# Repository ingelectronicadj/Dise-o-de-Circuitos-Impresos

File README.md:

# Repo Circuitos Impresos
Versionamiento de diversas placas PCB y diseños para integrados de soldadura superficial diseñados asiendo uso del software Eagle (Version Académica)

## IoT para determinar el peso al interior de un contenedor

## Estación Meteorologica remota - GSM

## Bases para sensor UV y de Color

## Control de 2 motores DC

## PCB para control de LED RGB 100W

## Modulador - Demodulador

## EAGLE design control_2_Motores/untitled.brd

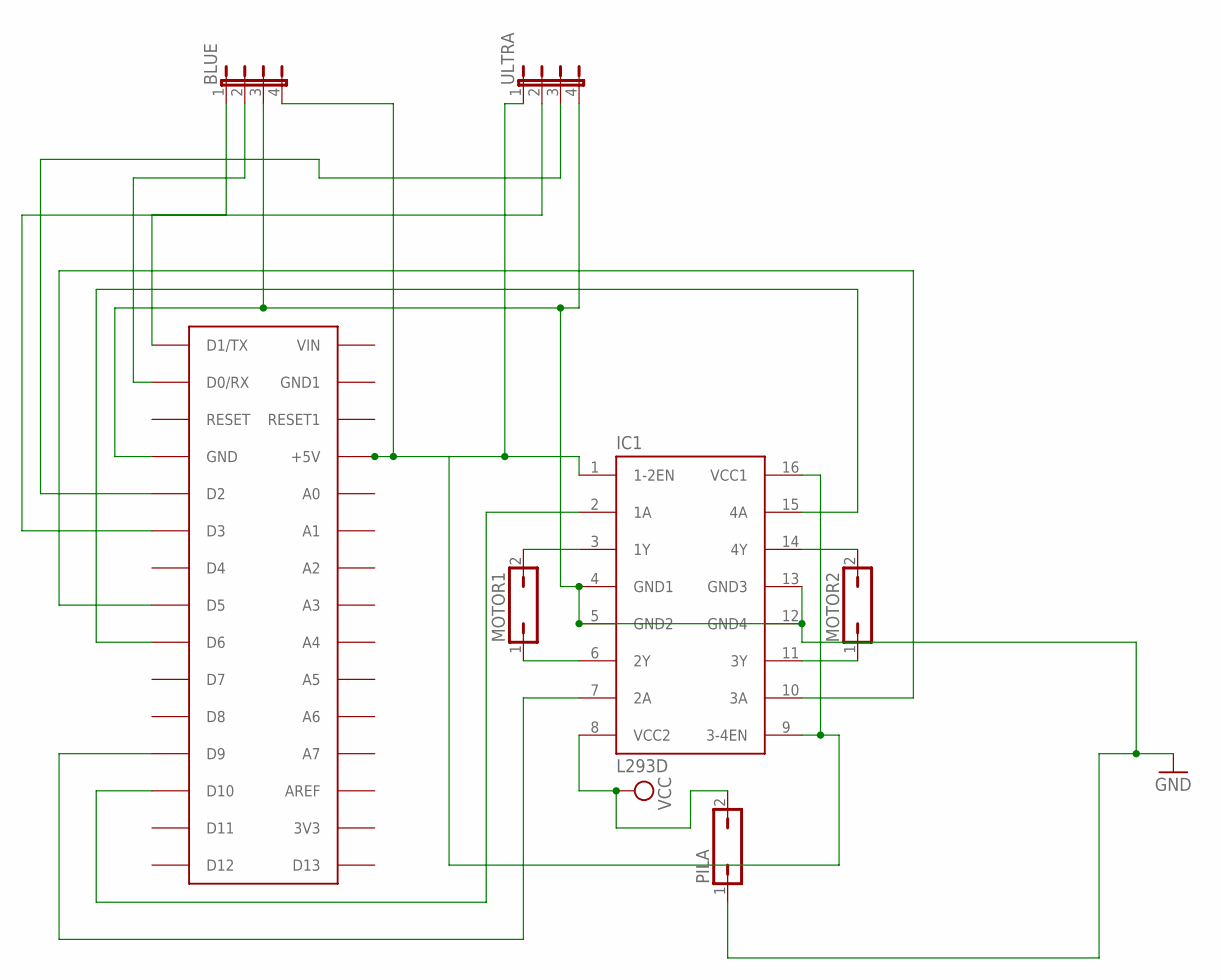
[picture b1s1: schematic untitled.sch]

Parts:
BLUE: JP4E; JP4
IC1: L293D; DIL16
MOTOR1, MOTOR2: JP1Q; JP1
PILA: JP1Q; JP1
U$1: ARDUINONANO; PDIP-32
ULTRA: JP4E; JP4

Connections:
GND: BLUE.3, IC1.4 (GND1), IC1.5 (GND2), IC1.12 (GND4), IC1.13 (GND3), PILA.1, U$1.GND, ULTRA.4
unnamed: IC1.10 (3A), U$1.D5
unnamed: IC1.15 (4A), U$1.D6
unnamed: IC1.7 (2A), U$1.D9
unnamed: IC1.2 (1A), U$1.D10
unnamed: BLUE.4, IC1.1 (1-2EN), IC1.9 (3-4EN), IC1.16 (VCC1), U$1.+5V, ULTRA.1
unnamed: BLUE.2, U$1.D0/RX
unnamed: BLUE.1, U$1.D1/TX
unnamed: IC1.3 (1Y), MOTOR1.2
unnamed: U$1.D3, ULTRA.2
unnamed: U$1.D2, ULTRA.3
unnamed: IC1.6 (2Y), MOTOR1.1
unnamed: IC1.11 (3Y), MOTOR2.1
unnamed: IC1.14 (4Y), MOTOR2.2
VCC: IC1.8 (VCC2), PILA.2

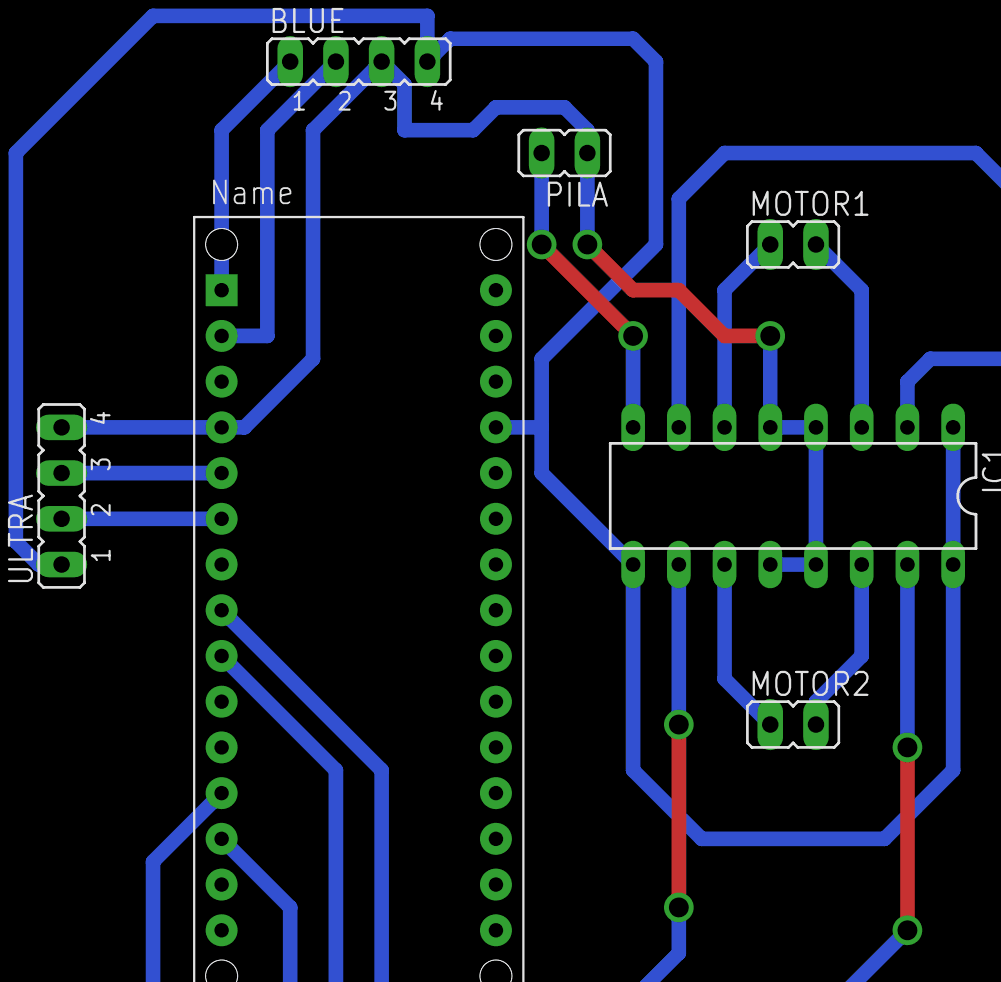
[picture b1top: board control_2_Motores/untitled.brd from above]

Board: 2 copper layers, 7 parts (0 on the bottom side), 15 nets.

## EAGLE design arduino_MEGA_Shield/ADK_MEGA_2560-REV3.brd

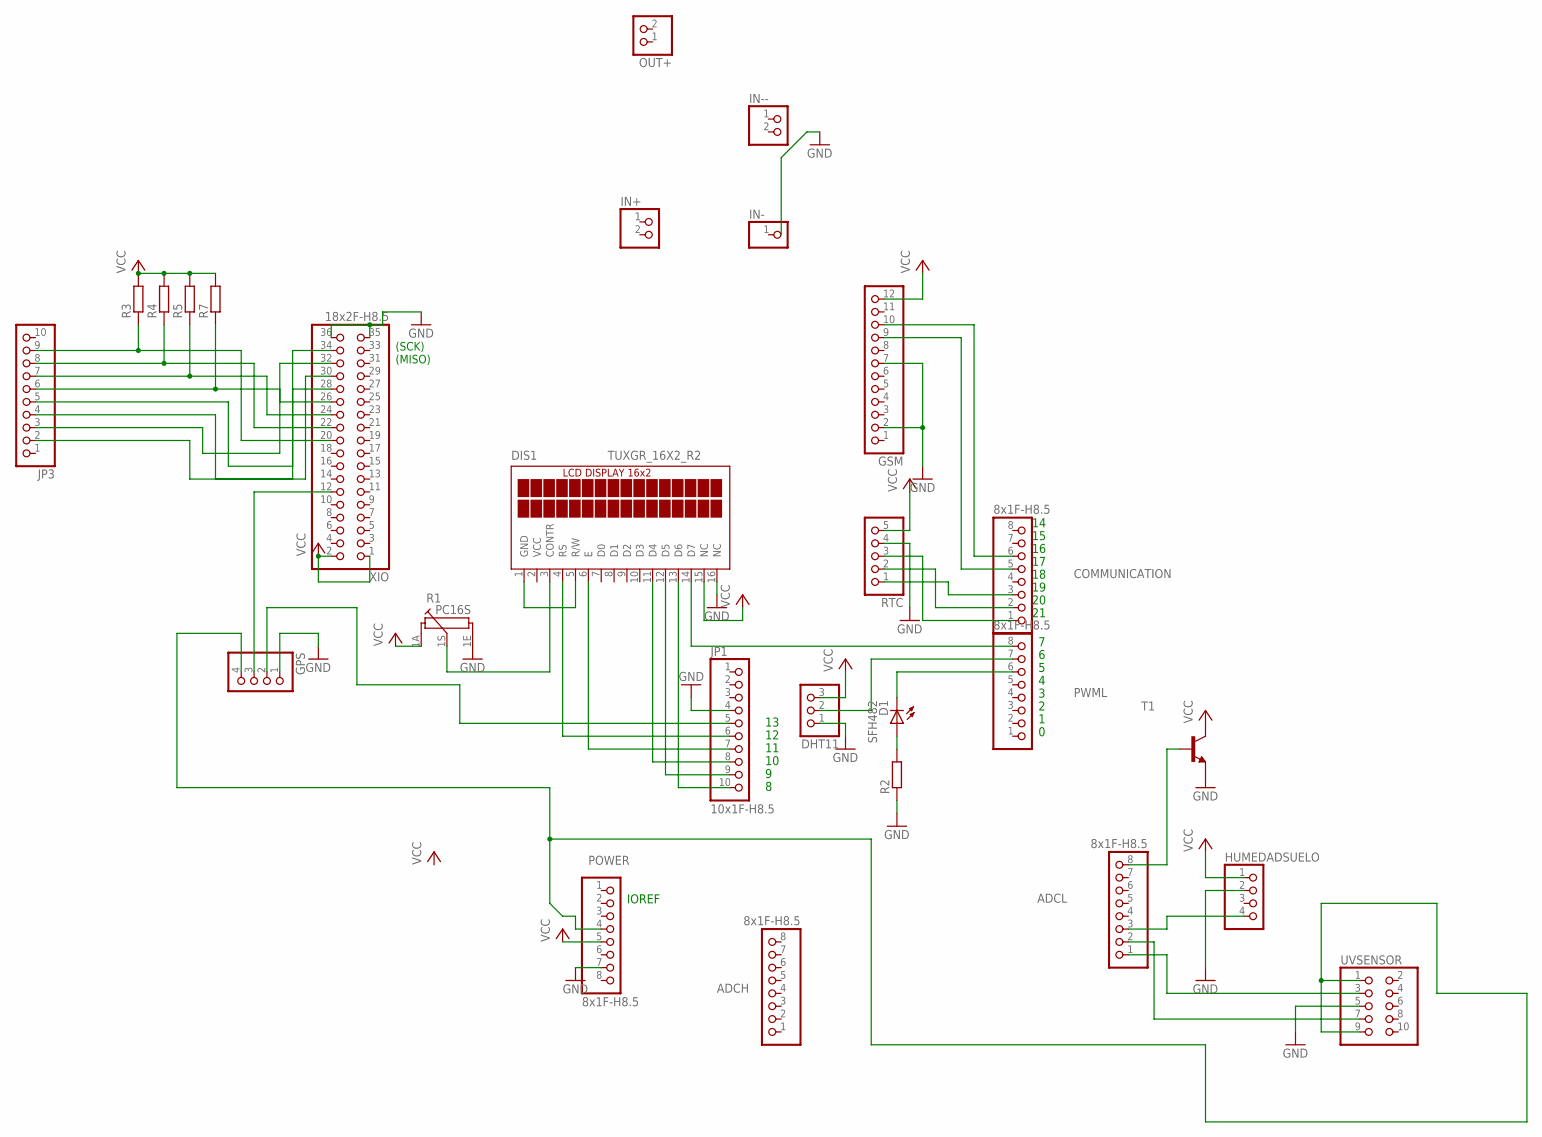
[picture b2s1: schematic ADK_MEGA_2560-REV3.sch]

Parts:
ADCH: 8x1F-H8.5; 1X08
ADCL: 8x1F-H8.5; 1X08
COMMUNICATION: 8x1F-H8.5; 1X08
D1: SFH482
DHT11: PINHD-1X3; 1X03
DIS1: TUXGR_16X2_R2
GPS: PINHD-1X4; 1X04
GSM: PINHD-1X12; 1X12
HUMEDADSUELO: PINHD-1X4; 1X04
IN+: PINHD-1X2; 1X02
IN-: PINHD-1X1; 1X01
IN--: PINHD-1X2; 1X02
JP1: 10x1F-H8.5; 1X10
JP3: PINHD-1X10/90; 1X10/90
OUT+: PINHD-1X2; 1X02
POWER: 8x1F-H8.5; 1X08
PWML: 8x1F-H8.5; 1X08
R1: PC16S
R2, R3, R4, R5, R7: R0204/7; 0204/7
RTC: PINHD-1X5; 1X05
T1: 2N2222-NPN-TO92-EBC; TO92-EBC
UVSENSOR: PINHD-2X5; 2X05
XIO: 18x2F-H8.5; 2X18

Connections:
GND: DHT11.1, DIS1.16 (NC), GPS.1, GSM.2, GSM.7, HUMEDADSUELO.2, JP1.4, POWER.7, R1.1E, R2.1, RTC.4, T1.E, UVSENSOR.5, XIO.35, XIO.36
unnamed: DIS1.3 (CONTR), R1.1S
unnamed: D1.K (C), PWML.6
unnamed: D1.A, R2.2
unnamed: DIS1.14 (D7), PWML.8
unnamed: DIS1.1 (GND), DIS1.5 (R/W)
unnamed: DIS1.13 (D6), JP1.10
unnamed: DIS1.12 (D5), JP1.9
unnamed: DIS1.11 (D4), JP1.8
unnamed: DIS1.6 (E), JP1.7
unnamed: DIS1.4 (RS), JP1.6
unnamed: GPS.2, JP1.5
unnamed: DHT11.2, PWML.7
unnamed: GPS.3, XIO.12
unnamed: COMMUNICATION.1, RTC.3
unnamed: COMMUNICATION.2, RTC.2
unnamed: COMMUNICATION.3, RTC.1
unnamed: ADCL.3, HUMEDADSUELO.4
unnamed: ADCL.8, T1.B
unnamed: ADCL.2, UVSENSOR.7
unnamed: ADCL.1, UVSENSOR.3
unnamed: COMMUNICATION.6, GSM.10
unnamed: COMMUNICATION.5, GSM.9
unnamed: JP3.9, R3.1, XIO.20
unnamed: JP3.8, R4.1, XIO.22
unnamed: JP3.7, R5.1, XIO.24
unnamed: JP3.6, R7.1, XIO.26
unnamed: GPS.4, POWER.4, UVSENSOR.1, UVSENSOR.9
unnamed: JP3.5, XIO.28
unnamed: JP3.4, XIO.30
unnamed: JP3.3, XIO.32
unnamed: JP3.2, XIO.34
VCC: DHT11.3, DIS1.2 (VCC), DIS1.15 (NC), GSM.12, HUMEDADSUELO.1, POWER.5, R1.1A, R3.2, R4.2, R5.2, R7.2, RTC.5, T1.C, XIO.1, XIO.2

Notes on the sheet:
(SCK)
(MISO)
IOREF

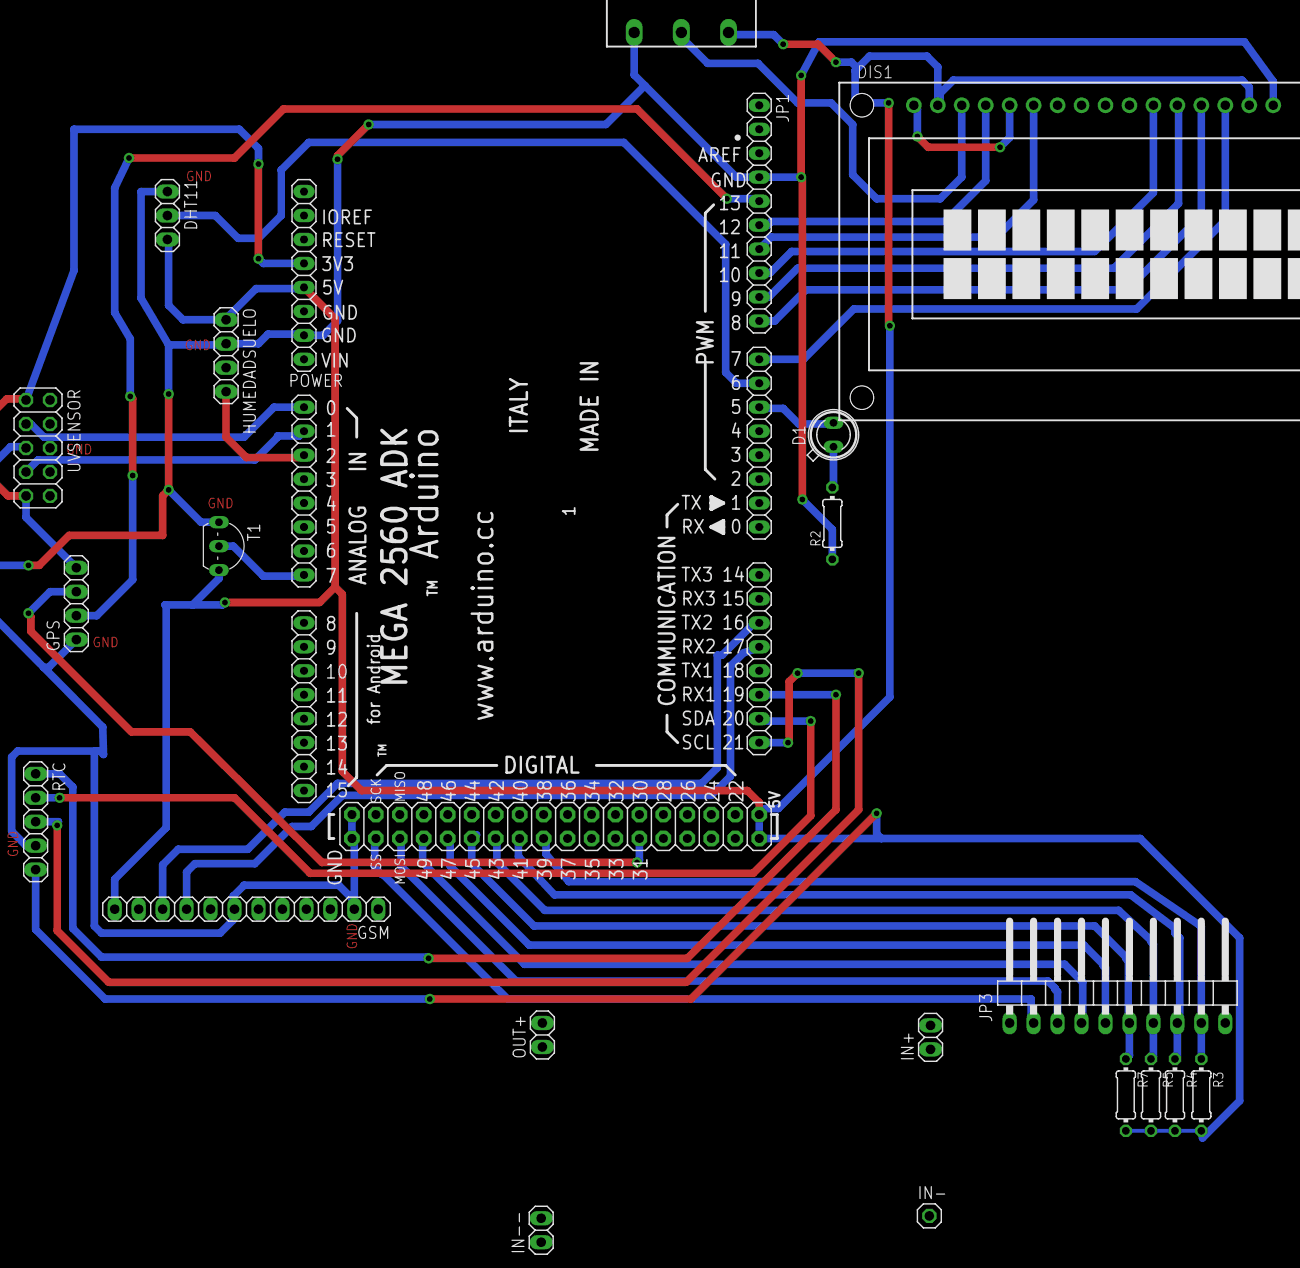
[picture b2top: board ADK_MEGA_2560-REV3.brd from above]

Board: 2 copper layers, 27 parts (0 on the bottom side), 33 nets.

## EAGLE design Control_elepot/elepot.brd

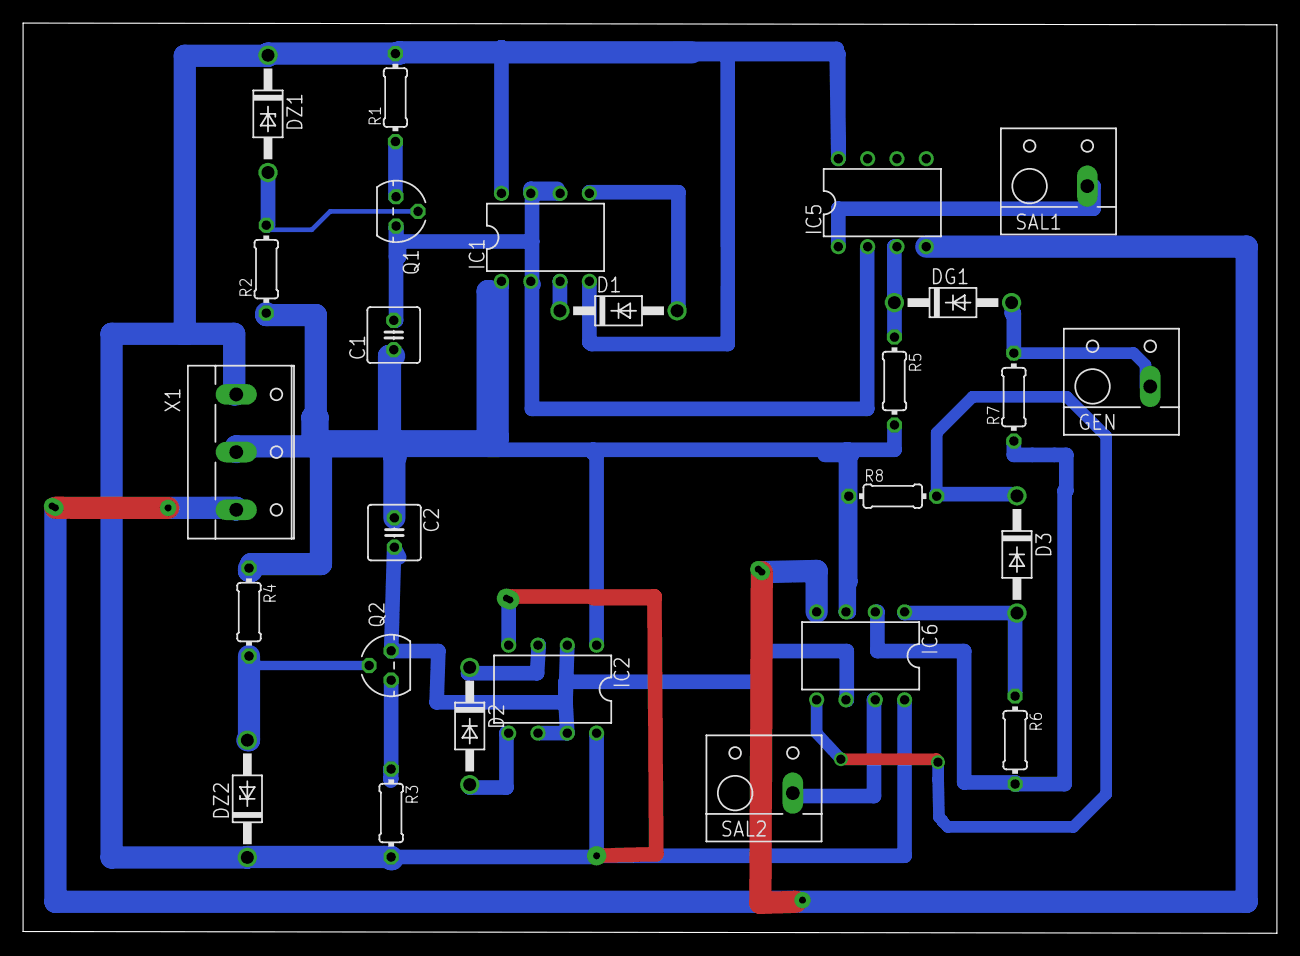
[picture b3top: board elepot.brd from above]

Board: 2 copper layers, 108.7 x 78.9 mm, 26 parts (0 on the bottom side), 22 nets.

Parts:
C1, C2: C025-050X050
D1, D2, D3: 1N4004; DO41-10
DG1: 1N4004; DO41-10
DZ1, DZ2: 1N4728; DO41Z10
GEN: W237-112
IC1, IC2: LM555N; DIL08
IC5, IC6: LF353N; DIL08
Q1, Q2: 2N3906; TO92
R1, R3: 10k; 0204/7
R2, R4: 2.2k; 0204/7
R5, R6, R7, R8: 0204/7
SAL1, SAL2: W237-112
X1: W237-103

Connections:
GND: IC1.1, IC2.1, IC6.3, R5.2, R8.1, X1.2
unnamed: DZ1.C, IC1.4, IC1.8, R1.2, X1.1
unnamed: Q1.3, R1.1
unnamed: DZ2.C, IC2.4, IC2.8, IC5.8, IC6.8, R3.2
unnamed: C1.1, C2.1, R2.1, R4.1
unnamed: DZ1.A, Q1.2, R2.2
unnamed: C1.2, IC1.2, IC1.6, IC1.7, Q1.1
unnamed: D1.C, IC1.3
unnamed: D1.A, IC1.5
unnamed: Q2.3, R3.1
unnamed: DZ2.A, Q2.2, R4.2
unnamed: C2.2, IC2.2, IC2.6, IC2.7, IC6.6, Q2.1
unnamed: D2.C, IC2.3
unnamed: D2.A, IC2.5
unnamed: DG1.C, IC5.3, R5.1
unnamed: DG1.A, GEN.1, R7.2
unnamed: IC5.4, IC6.4, X1.3
unnamed: IC6.2, R6.2, R7.1
unnamed: D3.C, IC6.5, R8.2
unnamed: D3.A, IC6.1, R6.1
unnamed: IC6.7, SAL2.1
unnamed: IC5.1, SAL1.1

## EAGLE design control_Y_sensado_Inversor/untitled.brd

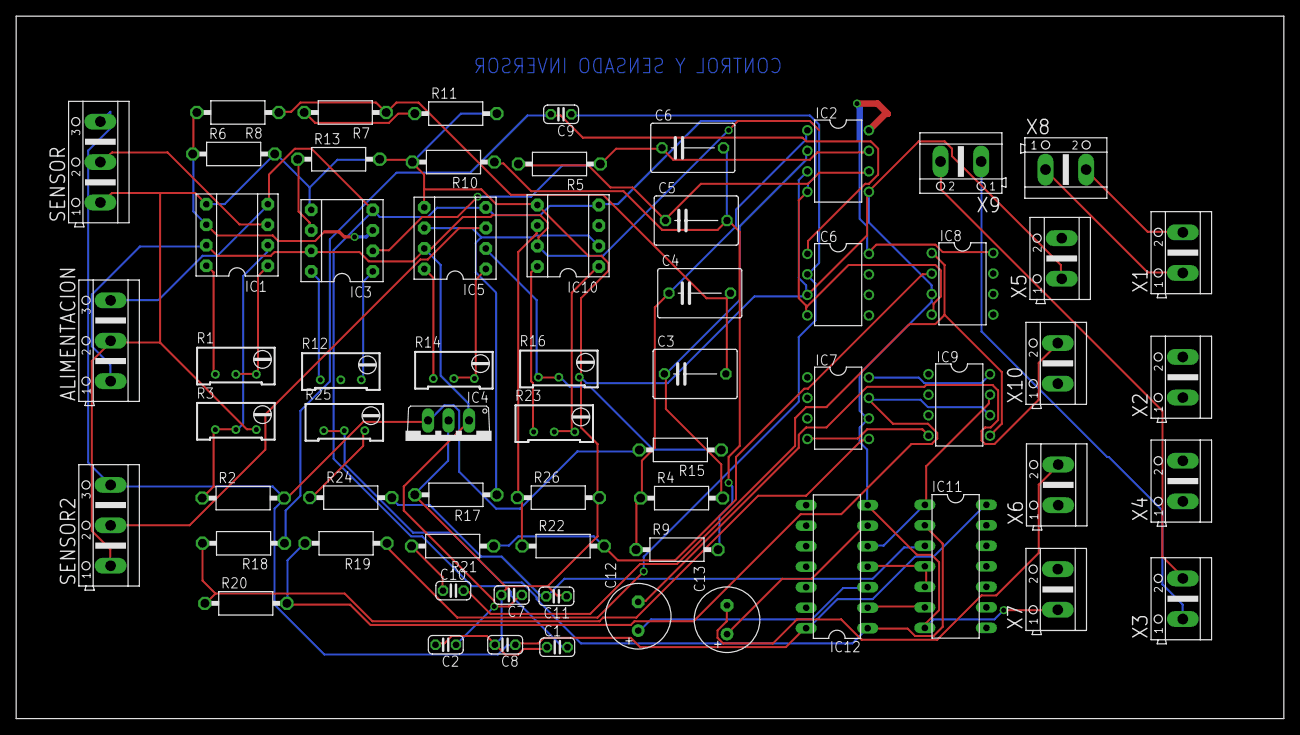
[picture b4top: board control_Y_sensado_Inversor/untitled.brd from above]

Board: 2 copper layers, 157.0 x 87.0 mm, 64 parts (0 on the bottom side), 50 nets.

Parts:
ALIMENTACION: AK500/3
C1: 0,1uf; C025-024X044
C2, C8: 0,1uF; C025-024X044
C3, C4, C5, C6: 1uf; C075-063X106
C7: 0,33uF; C025-024X044
C9, C10: 330pF; C025-024X044
C11: 10NF; C025-024X044
C12, C13: E3,5-8
IC1, IC3, IC5, IC10: INA128P; DIL08
IC2, IC6, IC7, IC8, IC9: LF353N; DIL08
IC4: 7805TV; TO220V
IC11: 74HC04N; DIL14
IC12: 74HC08N; DIL14
R1, R12, R14, R23: 20k; RTRIM64W
R2, R15: 15k; VMTA55
R3, R16: 5k; RTRIM64W
R4: 10k; VMTA55
R5: 3,9k; VMTA55
R6, R13, R17, R21, R22, R26: 1k; VMTA55
R7: 2,2k; VMTA55
R8: 3,3k; VMTA55
R9: 1,2k; VMTA55
R10: 1,5k; VMTA55
R11: 2k; VMTA55
R18, R19: 27k; VMTA55
R20: 39k; VMTA55
R24: 300; VMTA55
R25: 10k; RTRIM64W
SENSOR, SENSOR2: AK500/3
X1, X2, X3, X4, X5, X6, X7, X8, X9, X10: AK500/2

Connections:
-12V: ALIMENTACION.1, C2.1, C7.1, IC1.7, IC2.8, IC3.7, IC4.1, IC5.7, IC6.8, IC8.8, IC10.7
unnamed: IC1.1, R1.2, R1.3
unnamed: IC1.8, R1.1
unnamed: IC11.2, IC12.1, R25.1, R25.2
unnamed: IC5.2, R15.1, R16.1, R16.2
unnamed: C3.1, IC2.2, R4.2
unnamed: IC1.3, SENSOR.2
unnamed: C4.1, IC2.1, R4.1, R9.1
unnamed: IC1.2, R2.1, R3.1, R3.2
unnamed: C5.1, IC2.6, R5.2
unnamed: C6.1, IC2.7, IC3.2, R5.1
unnamed: C3.2, C4.2, R7.1, R8.1
unnamed: C5.2, C6.2, R9.2, R10.1
unnamed: IC1.6, IC3.3, R6.1, R8.2
unnamed: ALIMENTACION.2, C1.1, C2.2, C7.2, C8.2, C11.1, IC1.5, IC2.3, IC2.5, IC3.5, IC4.2, IC5.5, IC6.3, IC7.6, IC8.3, IC10.5, IC11.7, IC12.7, R3.3, R6.2, R10.2, R11.2, R13.2, R16.3, R17.2, R26.2, SENSOR.1, SENSOR2.1, X5.1, X7.1
unnamed: IC3.1, R12.3
unnamed: R7.2, R11.1
unnamed: IC3.8, R12.1
unnamed: IC3.6, R13.1
unnamed: IC5.1, R14.2, R14.3
unnamed: IC5.8, R14.1
unnamed: IC5.3, SENSOR2.2
unnamed: C12.+, IC12.3
unnamed: IC5.6, IC10.2, R17.1
unnamed: C9.1, IC6.2, R19.1
unnamed: C9.2, IC6.1, R18.1
unnamed: IC7.5, R18.2, R20.1
unnamed: IC7.7, IC9.6, R19.2, R20.2
unnamed: IC8.2, R21.1, R22.2
unnamed: C10.1, R21.2
unnamed: C10.2, IC8.1, IC9.5
unnamed: C11.2, IC11.3, R24.2
unnamed: ALIMENTACION.3, C1.2, IC1.4, IC2.4, IC3.4, IC5.4, IC6.4, IC8.4, IC10.4
unnamed: R24.1, R25.3
unnamed: IC10.1, R23.2, R23.3
unnamed: IC10.8, R23.1
unnamed: IC11.4, IC11.5, IC12.4
unnamed: IC10.6, R22.1, R26.1
unnamed: IC9.7, IC11.1, IC12.5
unnamed: C8.1, IC4.3, IC11.14, IC12.14, R2.2, R15.2, SENSOR.3, SENSOR2.3
unnamed: IC11.6, IC12.2
unnamed: C13.+, IC12.6
unnamed: C12.-, X10.2
unnamed: C13.-, X6.2
unnamed: X3.2, X9.2
unnamed: X3.1, X9.1
unnamed: X1.2, X8.2
unnamed: X1.1, X8.1
V+: IC7.8, IC9.8
V-: IC7.4, IC9.4

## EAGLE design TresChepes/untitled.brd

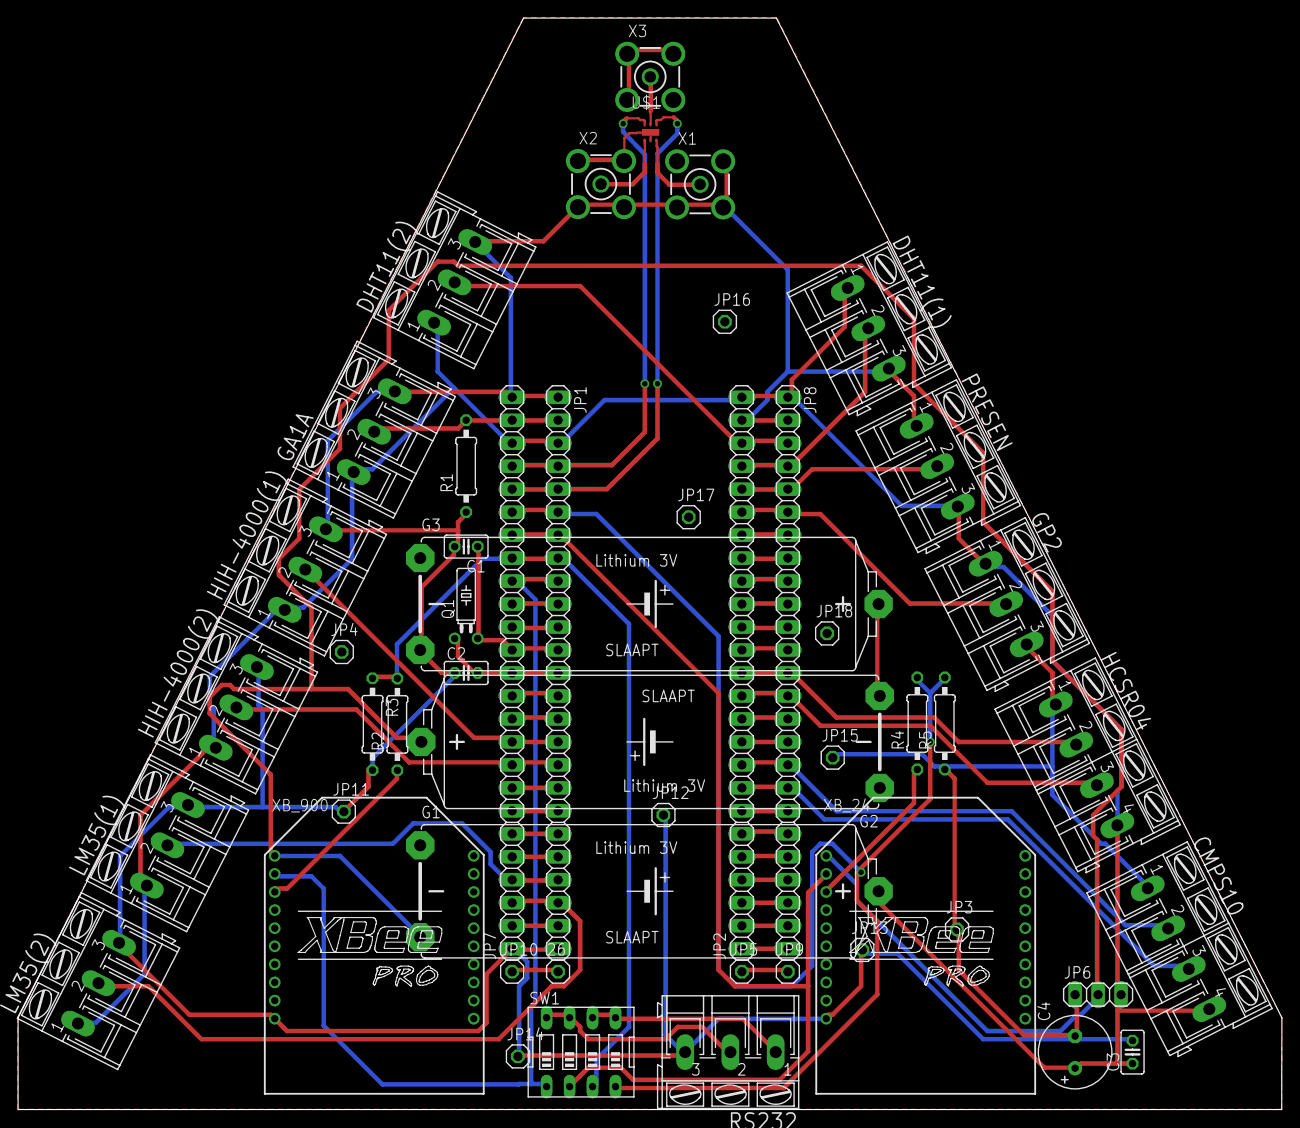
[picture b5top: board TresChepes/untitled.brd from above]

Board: 2 copper layers, 139.7 x 120.7 mm, 51 parts (0 on the bottom side), 58 nets.

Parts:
26: 1X01
C1, C2: 10; C025-025X050
C3: C025-025X050
C4: E3,5-8
CMPS10: AK300/4
DHT11(1), DHT11(2): AK300/3
G1, G2, G3: SL-160AA/PT
GA1A: AK300/3
GP2: AK300/3
HCSR04: AK300/4
HIH-4000(1), HIH-4000(2): AK300/3
JP1, JP2, JP7, JP8: 1X25
JP3, JP4, JP5, JP9, JP10, JP11, JP12, JP13, JP14, JP15, JP16, JP17, JP18: 1X01
JP6: 1X03
LM35(1), LM35(2): AK300/3
PRESEN: AK300/3
Q1: TC26H
R1, R2, R3, R4, R5: 0207/10
RS232: AK300/3
SW1: EDG-04
U$1: SPDT; SO70-6SPDT
X1, X2, X3: BU-SMA-V
XB_24, XB_900: XBEE-PRO

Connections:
+3V3: G1.-, G2.+, JP6.2, XB_24.1, XB_900.1
GND: C1.2, C2.1, C3.2, C4.-, CMPS10.1, DHT11(1).3, DHT11(2).3, G3.-, GA1A.3, GP2.3, HCSR04.1, HIH-4000(1).3, HIH-4000(2).3, JP1.1, JP1.25, JP2.24, JP3.1, JP4.1, JP6.1, JP7.1, JP7.25, JP8.2, JP11.1, JP12.1, JP13.1, JP14.1, JP15.1, JP16.1, JP17.1, JP18.1, LM35(1).3, LM35(2).3, PRESEN.1, R1.1, R3.2, R5.1, RS232.3, U$1.2, X1.2, X1.3, X1.4, X1.5, X2.2, X2.3, X2.4, X2.5, X3.2, X3.3, X3.4, X3.5, XB_24.10, XB_900.10
unnamed: JP1.23, JP7.3, LM35(2).2
unnamed: JP1.22, JP7.4, LM35(1).2
unnamed: HIH-4000(2).2, JP1.17, JP7.9
unnamed: CMPS10.2, JP2.9, JP8.17
unnamed: GA1A.2, JP1.2, JP7.24, R1.2
unnamed: C1.1, JP1.12, JP7.14, Q1.2
unnamed: CMPS10.3, JP2.8, JP8.18
unnamed: GP2.2, JP2.20, JP8.6
unnamed: HCSR04.2, JP2.13, JP8.13
unnamed: DHT11(2).2, JP2.23, JP8.3
unnamed: DHT11(1).2, JP2.22, JP8.4
unnamed: JP2.21, JP8.5, PRESEN.2
unnamed: JP1.9, JP7.17, SW1.1, XB_900.2
unnamed: HCSR04.3, JP2.12, JP8.14
unnamed: JP1.8, JP7.18, R2.2, R3.1, SW1.3
unnamed: JP1.6, JP7.20, R4.2, R5.2, SW1.4
unnamed: JP1.7, JP7.19, SW1.2, XB_24.2
unnamed: RS232.1, SW1.5, SW1.6
unnamed: RS232.2, SW1.7, SW1.8
unnamed: HIH-4000(1).2, JP1.16, JP7.10
unnamed: G2.-, G3.+
unnamed: JP1.4, JP7.22, U$1.P$6
unnamed: C2.2, JP1.13, JP7.13, Q1.1
unnamed: 26.1, JP10.1
unnamed: JP5.1, JP9.1
unnamed: JP1.24, JP7.2
unnamed: JP1.20, JP7.6
unnamed: JP1.21, JP7.5
unnamed: JP1.19, JP7.7
unnamed: JP1.18, JP7.8
unnamed: JP2.1, JP8.25
unnamed: JP2.4, JP8.22
unnamed: JP2.3, JP8.23
unnamed: JP2.2, JP8.24
unnamed: JP2.5, JP8.21
unnamed: JP2.6, JP8.20
unnamed: JP2.7, JP8.19
unnamed: JP2.10, JP8.16
unnamed: JP2.11, JP8.15
unnamed: JP1.15, JP7.11
unnamed: JP1.14, JP7.12
unnamed: JP1.10, JP7.16
unnamed: JP1.11, JP7.15
unnamed: JP2.19, JP8.7
unnamed: JP2.18, JP8.8
unnamed: JP2.17, JP8.9
unnamed: JP2.16, JP8.10
unnamed: JP2.15, JP8.11
unnamed: JP2.14, JP8.12
unnamed: JP1.5, JP7.21, U$1.4
unnamed: R2.1, XB_900.3
unnamed: R4.1, XB_24.3
unnamed: U$1.1, X2.1
unnamed: U$1.3, X1.1
unnamed: U$1.5, X3.1
VCC: C3.1, C4.+, CMPS10.4, DHT11(1).1, DHT11(2).1, G1.+, GA1A.1, GP2.1, HCSR04.4, HIH-4000(1).1, HIH-4000(2).1, JP1.3, JP2.25, JP6.3, JP7.23, JP8.1, LM35(1).1, LM35(2).1, PRESEN.3

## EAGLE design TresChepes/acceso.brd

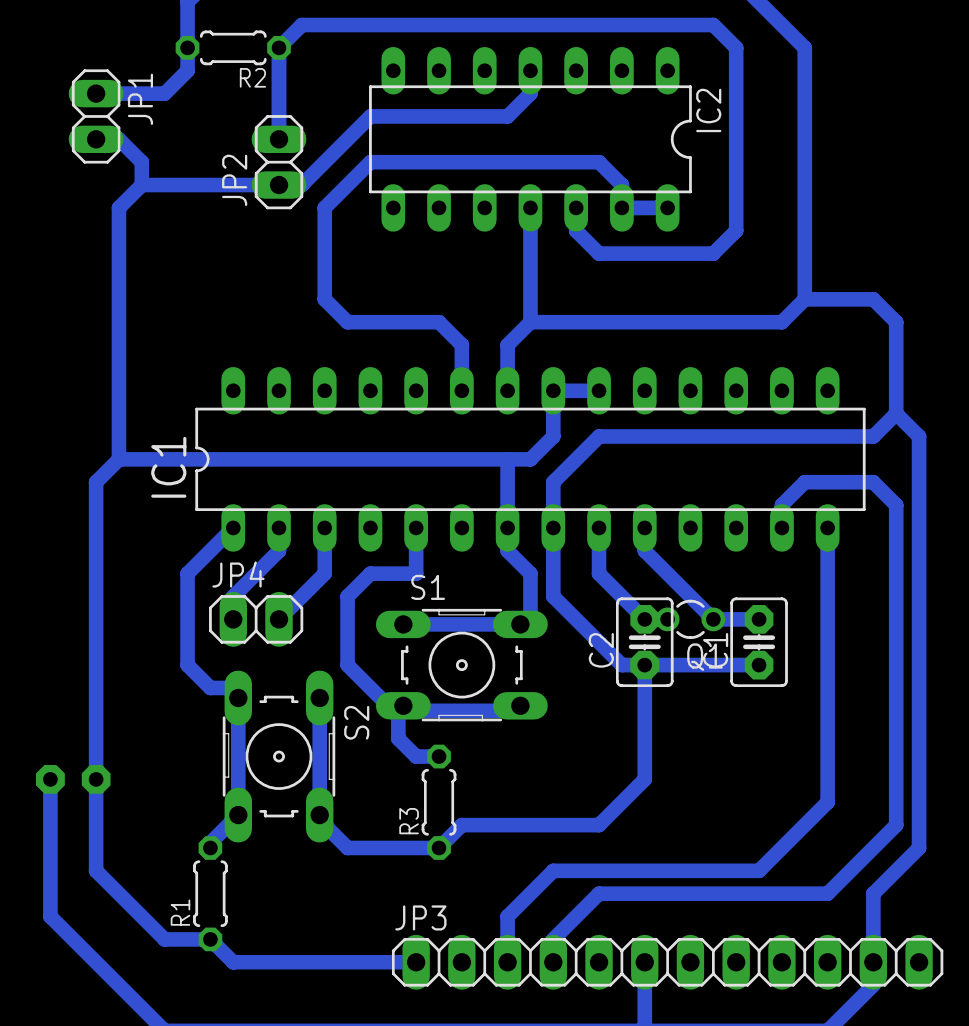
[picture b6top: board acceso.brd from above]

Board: 2 copper layers, 15 parts (1 on the bottom side), 12 nets.

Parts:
C1, C2, C3: C2.5-3
IC1: MEGA8-P; DIL28-3
IC2: LM324N; DIL14
JP1, JP2, JP4: 1X02
JP3: 1X12
Q1: TC26V
R1, R2, R3: 0204/5
S1, S2: B3F-10XX

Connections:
5V: C3.1, IC1.7, IC1.20, IC1.21, IC2.4, JP1.2, JP2.1, JP3.1, R1.1, S1.1, S1.2
GND: C1.1, C2.1, C3.2, IC1.8, IC1.22, IC2.11, JP1.1, JP3.6, JP3.11, R2.2, R3.1, S2.1, S2.2
unnamed: IC1.23, IC2.13, IC2.14
unnamed: IC1.14, JP3.3
unnamed: IC1.13, JP3.4
unnamed: IC1.5, R3.2, S1.3, S1.4
unnamed: IC1.3, JP4.2
unnamed: IC2.12, JP2.2, R2.1
unnamed: IC1.2, JP4.1
unnamed: C2.2, IC1.9, Q1.2
unnamed: C1.2, IC1.10, Q1.1
unnamed: IC1.1, R1.2, S2.3, S2.4

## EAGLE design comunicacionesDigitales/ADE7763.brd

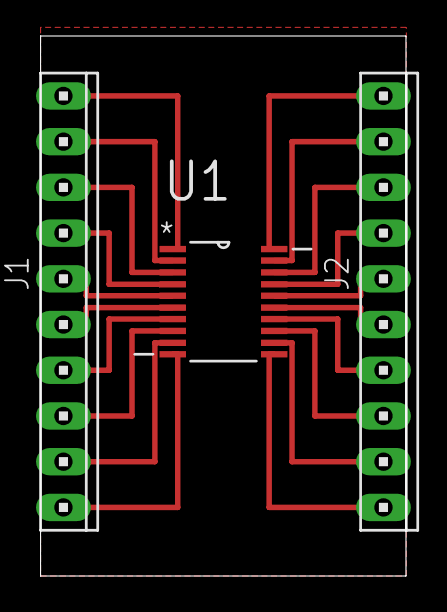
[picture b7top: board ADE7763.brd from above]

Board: 2 copper layers, 20.3 x 30.0 mm, 3 parts (0 on the bottom side), 20 nets.

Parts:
J1, J2: 10X10MTA
U1: ADE7763ARSZ; SOP65P640X120-20N

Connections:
unnamed: J1.10, U1.1
unnamed: J1.9, U1.2
unnamed: J1.8, U1.3
unnamed: J1.7, U1.4
unnamed: J1.6, U1.5
unnamed: J1.5, U1.6
unnamed: J1.4, U1.7
unnamed: J1.3, U1.8
unnamed: J1.2, U1.9
unnamed: J1.1, U1.10
unnamed: J2.1, U1.11
unnamed: J2.2, U1.12
unnamed: J2.3, U1.13
unnamed: J2.4, U1.14
unnamed: J2.5, U1.15
unnamed: J2.6, U1.16
unnamed: J2.7, U1.17
unnamed: J2.8, U1.18
unnamed: J2.9, U1.19
unnamed: J2.10, U1.20

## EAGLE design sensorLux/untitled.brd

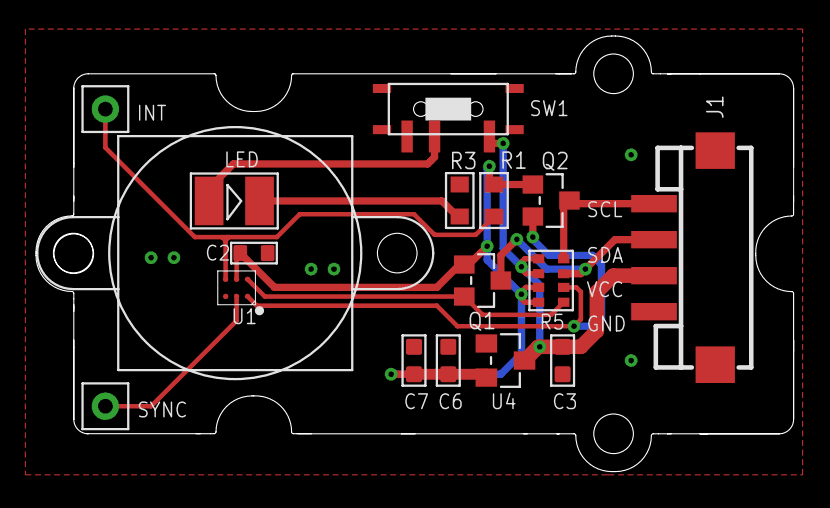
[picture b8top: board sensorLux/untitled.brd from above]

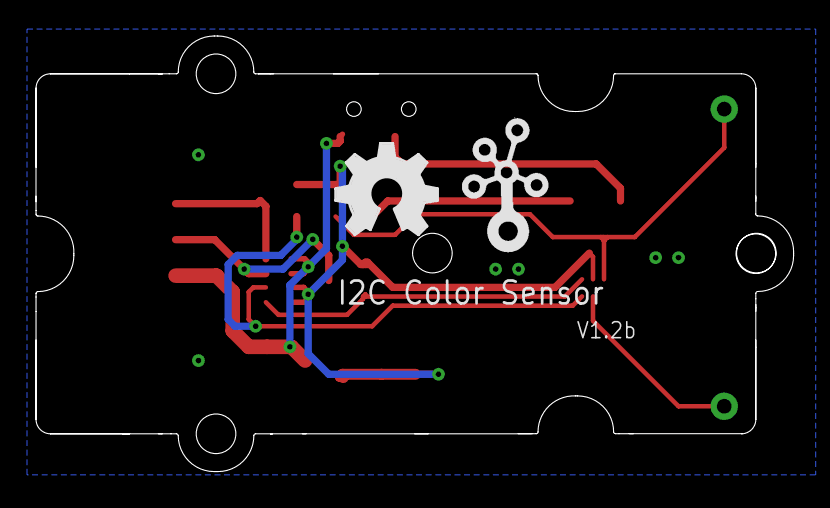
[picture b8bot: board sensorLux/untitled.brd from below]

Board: 2 copper layers, 42.1 x 24.2 mm, 20 parts (2 on the bottom side), 11 nets.

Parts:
C2: 100nF; 0603_S
C3, C6: 1uF; C0603
C7: 100nF; C0603
INT: CK_1X1
J1: 4P-SMD-2.0
LED: White-3528; LED1210
Q1, Q2: BSN20; SOT23
R1: 10k; 0603
R3: 330; 0603
R5: 10k; R1206-8
SW1: SWITCH_4X7; 4*8_SW
SYNC: CK_1X1
U1: TCS3414CS-COLOR; TCS3414CS
U3: LENS_HOOD
U4: XC6206P332MR-G; SOT23
U$1: TWIGLOGO
U$2: 2U-DIM-W/-DRILL
U$3: OSHW_FILLX200_NOTEXT

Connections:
3V3: C2.1, C6.2, C7.2, Q1.1, Q2.1, R1.1, R5.7, R5.8, U1.B2, U4.2
GND: C2.2, C3.1, C6.1, C7.1, J1.4, J1.SS1, J1.SS2, R3.1, U1.A3, U4.1
HSCL: J1.1, Q2.3, R5.4
HSDA: J1.2, Q1.3, R5.3
INT: INT.P$1, R1.2, U1.B3
unnamed: LED.1, SW1.COM
unnamed: LED.2, R3.2
SCL: Q2.2, R5.2, U1.A1
SDA: Q1.2, R5.1, U1.B1
SYNC: SYNC.P$1, U1.A2
VCC: C3.2, J1.3, R5.5, R5.6, SW1.A, U4.3

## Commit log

2016-11-05 Se añade pcb para sensor integrado ML8511
2016-11-05 Se añade diseño para sensor de color encapsulado tcs3200
2016-11-05 Se añade diseño IoT usando GSM y atmega 328
2016-11-05 Se diseña shield para micro arduino MEGA
2016-11-05 Se añade diseño de integrado para modular/demodular (celda de Gilbert)
2016-11-05 Se añade diseño IoT para sensar de manera remota el peso al interior de un contenedor
2016-11-05 Se añade PCB para IoT invernaderos con sensado y control de manera remota
2016-11-05 Se añade PCB para control de LED RGB de 100W
2016-11-05 Se añade PCB para el control de direccion de 2 motores DC
2016-11-05 Se añade PCB para esquema de sensado de una estacion meteorologica remota usando el modulo de comunicacion GSM
2016-11-05 Se añade PCB para el control y sensado de un Inversor AC/DC
2016-11-05 Se añade PCB de un flyback-forward
2016-11-06 Se añaden imagenes al README
